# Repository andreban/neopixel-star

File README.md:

# NeoPixel Star

A star-shaped NeoPixel board in the spirit of the Adafruit Jewel. The outline is the exact yellow
sparkle from the [Modern Web Guidance logo](reference/mwg-logo.svg), uniformly scaled. Nine
addressable RGB LEDs: one in the centre, one in each of the 8 points.

| SMD ([smd/](smd/README.md)) | Hot-plate ([hotplate/](hotplate/README.md): [v1](hotplate/v1/README.md) / [v2](hotplate/v2/README.md)) | Through-hole ([tht/](tht/README.md)) | XIAO ([xiao/](xiao/README.md)) |
|---|---|---|---|
|  |  |  |  |
| 50 mm · 9 × WS2812B (5050) | 50 mm · 9 × WS2812B-Mini (3535) | 55 mm · 9 × WS2812D-F5 (5 mm) | 60 mm · 9 × WS2812B-Mini (3535) |
| Fab-assembled, parts on both sides | Front reflowed on a hot plate, back soldered by iron | Hand-soldered | Hot-plate front, Seeed XIAO plugged into female headers on the back |
| 74AHCT1G125 level shifter, 100 nF per LED | 0603 passives; [v1](hotplate/v1/README.md) with level shifter, [v2](hotplate/v2/README.md) direct 3.3 V data | LEDs take 3.3 V data directly | Own microcontroller: plug in USB-C and program it |

All versions share:

- A JST-PH 2.0 mm 3-pin connector on the back, cable toward the top point, pins labelled `5V / DIN / GND`
  (except the XIAO version, which has a USB-C microcontroller board there instead)
- Yellow solder mask, black silkscreen, ENIG, with the MWG logo in exposed gold on the back
- 2 layers, 1.6 mm. Front is a solid 5 V pour, back a solid GND pour
- The same data order, so the same code drives any of them

> **Status:** all designs pass KiCad ERC and DRC, including a check that each board matches its
> schematic. None has been manufactured or tested yet. Treat the first order as a prototype run.

## Wiring

The [XIAO version](xiao/README.md) needs none: it has its own microcontroller and USB-C. The others
connect through J1:

| J1 pin | Signal | Connect to |
|---|---|---|
| 1 | 5V | MCU board's 5 V / VBUS / USB pin, or an external 5 V supply |
| 2 | DIN | Any GPIO (3.3 V or 5 V logic) |
| 3 | GND | GND |

The data chain is: LED1 in the centre, then the top point, then clockwise (index 0 = centre,
1 = top, 2 = top-right, … 8 = top-left).

Minimal Arduino sketch ([Adafruit NeoPixel](https://github.com/adafruit/Adafruit_NeoPixel)):

```cpp
#include <Adafruit_NeoPixel.h>

Adafruit_NeoPixel star(9, /* DIN pin */ 6, NEO_GRB + NEO_KHZ800);

void setup() {
  star.begin();
  star.setBrightness(80);  // keep USB-powered boards within budget, see below
}

void loop() {
  for (int i = 0; i < 9; i++) {          // light each LED in turn, centre first
    star.clear();
    star.setPixelColor(i, star.Color(255, 180, 0));
    star.show();
    delay(200);
  }
}
```

**Power:** at full white each board draws about 540 mA, which is more than many USB ports and
cables supply. When powering from the MCU's USB 5 V pin, cap the brightness in software:

```cpp
strip.setBrightness(80);                        // Adafruit_NeoPixel, 0-255
FastLED.setMaxPowerInVoltsAndMilliamps(5, 400); // FastLED
```

Don't power it from a 3V3 pin. The LEDs need 3.7–5.3 V, and a 3.3 V regulator can't supply the current.

## Ordering

Each version has its own Gerbers in `<version>/fab/`, which work at both JLCPCB and PCBWay.
Silkscreen colour is an order option, not part of the files.

**Board options:** 2 layers · 1.6 mm FR-4 · **yellow** solder mask · **black** silkscreen ·
**ENIG** surface finish (this is what makes the logo gold) · 1 oz copper.

Version-specific steps, BOM and placement files: [SMD](smd/README.md#ordering) ·
[hot-plate v1](hotplate/v1/README.md#ordering) / [v2](hotplate/v2/README.md#ordering) · [through-hole](tht/README.md#ordering).

## Opening in KiCad or EasyEDA

Each version is a self-contained KiCad 10 project in `<version>/kicad/`. Its symbols and footprints
come from the project's own libraries, so no global libraries are needed. `<version>/easyeda/` has
the project zipped for EasyEDA Pro (*File → Import → KiCad*) and the exact outline as DXF. See the
[SMD notes](smd/README.md#opening-in-kicad-or-easyeda) for EasyEDA's via rule and expected warnings.

## Repository layout

| Path | Contents |
|---|---|
| `smd/`, `hotplate/v1/`, `hotplate/v2/`, `tht/`, `xiao/` | One folder per version: `README.md`, `kicad/` (project and libraries), `fab/` (Gerbers, BOM, placement), `easyeda/`, `docs/` (renders, assembly drawings, schematic PDF) |
| `scripts/` | Generators: everything in the version folders except the READMEs is built from these |
| `scripts/common/` | Code shared by all versions: outline, logo, design rules, board and schematic helpers |
| `scripts/smd/`, `scripts/hotplate/v1/`, `scripts/hotplate/v2/`, `scripts/tht/`, `scripts/xiao/` | Per version: `parts.py` (parts and nets), `layout.py` (placement and routing), `schematic.py` |
| `reference/` | The source logo SVG |
| `PLAN.md` | Design decisions and their reasoning |
| `AGENTS.md` | How to change the design (for AI agents and humans) |

## Rebuilding

KiCad 10 must be installed. It is found in its standard install location, or set `KICAD_DIR` to the
installation directory.

```sh
python scripts/build_all.py          # all versions
python scripts/build_all.py tht      # one version: smd, hotplate, hotplate/v1, hotplate/v2, tht or xiao
```

For each version, this regenerates the schematic and board, refills the pours with KiCad's zone
filler, and runs ERC and DRC with schematic parity. The build stops on any violation. It then
exports the Gerbers, the JLCPCB/PCBWay BOM and placement files, the EasyEDA package, the renders and
the assembly drawings (SVG, plus a printable PDF).

## Credits

The board outline and back-side artwork use the Modern Web Guidance logo from
[developer.chrome.com](https://developer.chrome.com/). Inspired by the
[Adafruit NeoPixel Jewel](https://www.adafruit.com/product/2226).

## License

[Apache License 2.0](LICENSE).

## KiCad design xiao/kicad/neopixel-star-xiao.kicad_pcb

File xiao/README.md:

# NeoPixel Star: XIAO version

A self-contained star: a [Seeed Studio XIAO](https://wiki.seeedstudio.com/SeeedStudio_XIAO_Series_Introduction/)
on the back runs the LEDs and connects over its own USB-C. No separate microcontroller, no cable to
wire up. The front is the [hot-plate v2](../hotplate/v2/README.md) design (3535 LEDs that take
3.3 V data directly), so it reflows the same way. The XIAO plugs into two female headers on the
back, so it can come out again (to reuse it, or swap in another model). 60 mm.

| Front | Back |
|---|---|
|  |  |
|  |  |
|  |  |

Schematic: [docs/schematic.pdf](docs/schematic.pdf)

Assembly drawing, front and back, for printing: [docs/assembly.pdf](docs/assembly.pdf)

> **Status:** passes KiCad ERC and DRC, including schematic parity. Not manufactured or tested yet.

## Which XIAO

Any of them. All XIAO boards share the same 14 edge pins (`D0`–`D10`, `3V3`, `GND`, `5V`), and the
board only uses three: `5V`, `GND` and `D3`. The pads some models have underneath aren't used.

The two Raspberry Pi ones are the obvious choice. Both are cheap and well supported in Arduino,
MicroPython and CircuitPython:

| XIAO | Seeed SKU | LCSC | `D3` is |
|---|---|---|---|
| RP2350 (in the BOM) | 102010550 | C41882923 | GPIO5 |
| RP2040 | 102010428 | C22184628 | GPIO29 |

The ESP32-C3/C6/S3 and nRF52840 XIAOs work the same way.

## How it differs from hot-plate v2

- **No J1.** Power and data come from the XIAO: its `5V` pin is USB VBUS, and its `D3` drives the
  chain through `R1` (330 Ω). The WS2812B-MINI-V6 switches at $0.55 \times V_{DD}$ ($2.75\text{ V}$
  at $5\text{ V}$), so the XIAO's 3.3 V output drives it directly.
- **60 mm instead of 50 mm.** The XIAO's pin rows are 15.24 mm apart, through the middle of the
  board. The LED ring, its vias and the back-side data hops are v2's, scaled up so they clear the
  pins.
- **In female headers, not flat.** A USB-C plug's moulded grip is about 12.5 × 6.5 mm. Soldered
  flat, the plug would hit the board, because the notches between the points are too narrow for it,
  and cutting a slot for it wrecks the logo's shape. The headers lift the module 11 mm (8.5 mm socket
  plus the XIAO's 2.5 mm header plastic), so any plug clears the board. The module's top is about
  14.5 mm above the star's back. Vias are tented, so they can sit under the module.
- **Artwork all on the front.** The module covers the back. The credit line sits above the pin rows,
  the gold logo between them, and the title (0.9 mm instead of 1 mm, to fit) below them.

## Parts

| Ref | Side | Part | LCSC |
|---|---|---|---|
| LED1–LED9 | front | Worldsemi WS2812B-MINI-V6, 3535 | C52941386 |
| C1 | front | 10 µF 0603 X5R (Samsung CL10A106KP8NNNC) | C19702 |
| R1 | front | 330 Ω 0603 (UNI-ROYAL 0603WAF3300T5E) | C23138 |
| U1 | back | Seeed Studio XIAO RP2350 (102010550), or XIAO RP2040 (102010428, C22184628), or any XIAO | C41882923 |
| — | back | 2 × 1x7 female header, 2.54 mm, 8.5 mm tall (HCTL PM254-1-07-Z-8.5) | C2897370 |
| — | on the XIAO | 2 × 1x7 male pin header, 2.54 mm, 2.5 mm plastic (HCTL PZ254-1-07-Z-8.5) | C2894930 |

## Assembly

1. **Bake the LEDs first.** They are moisture-sensitive (MSL 5a): 120 °C for 4 hours for loose
   parts (or 70–75 °C for 24 hours), then solder them within 24 hours.
2. **Front, on the hot plate.** Order a solder-paste stencil with the boards (front side only).
   Paste the front, then place R1, C1 and the 9 LEDs. Each LED's pin-1 corner matches the `1` on
   its silkscreen outline. Reflow with the back of the board flat on the plate. Aim for a 245 °C
   peak and don't linger: about 45–90 s above 217 °C.
3. **Male headers on the XIAO.** Plug the two male headers into the female ones so they stay
   straight and parallel, then put the XIAO on top, component side up, and solder its 14 pins.
4. **Female headers on the star, with an iron.** Push the female headers' pins through the star
   from the back, with the XIAO still plugged in as a jig and its USB-C toward the top point (the
   outline on the back silkscreen shows where). Solder the 14 pins on the star's front and trim
   them flush.
5. Unplug the XIAO and check with a multimeter that 5V and GND aren't shorted, then plug it back
   in.

## Code

Same data order as the other versions: index 0 is the centre, 1 the top point, then clockwise. Data
is on `D3`. With [Adafruit NeoPixel](https://github.com/adafruit/Adafruit_NeoPixel) in Arduino:

```cpp
#include <Adafruit_NeoPixel.h>

Adafruit_NeoPixel star(9, D3, NEO_GRB + NEO_KHZ800);

void setup() {
  star.begin();
  star.setBrightness(80);  // USB-powered: stay within the port's budget
}

void loop() {
  for (int i = 0; i < 9; i++) {
    star.clear();
    star.setPixelColor(i, star.Color(255, 180, 0));
    star.show();
    delay(200);
  }
}
```

In CircuitPython it's `neopixel.NeoPixel(board.D3, 9)`. MicroPython uses GPIO numbers:

```python
neopixel.NeoPixel(machine.Pin(5), 9)   # XIAO RP2350
neopixel.NeoPixel(machine.Pin(29), 9)  # XIAO RP2040
```

**Power:** the LEDs draw from USB through the XIAO's `5V` pin, up to about 540 mA at full white.
That's more than a USB 2.0 port is required to supply, so cap the brightness (above) or with
`FastLED.setMaxPowerInVoltsAndMilliamps(5, 400)`.

## Ordering

`fab/neopixel-star-xiao-gerbers.zip`, with the board options from the
[main README](../README.md#ordering). Add a **stencil for the front (top) layer**. `fab/jlcpcb/` and
`fab/pcbway/` also have BOM and placement files if you'd rather have the front assembled. Leave U1
out of the assembly order and solder it yourself.

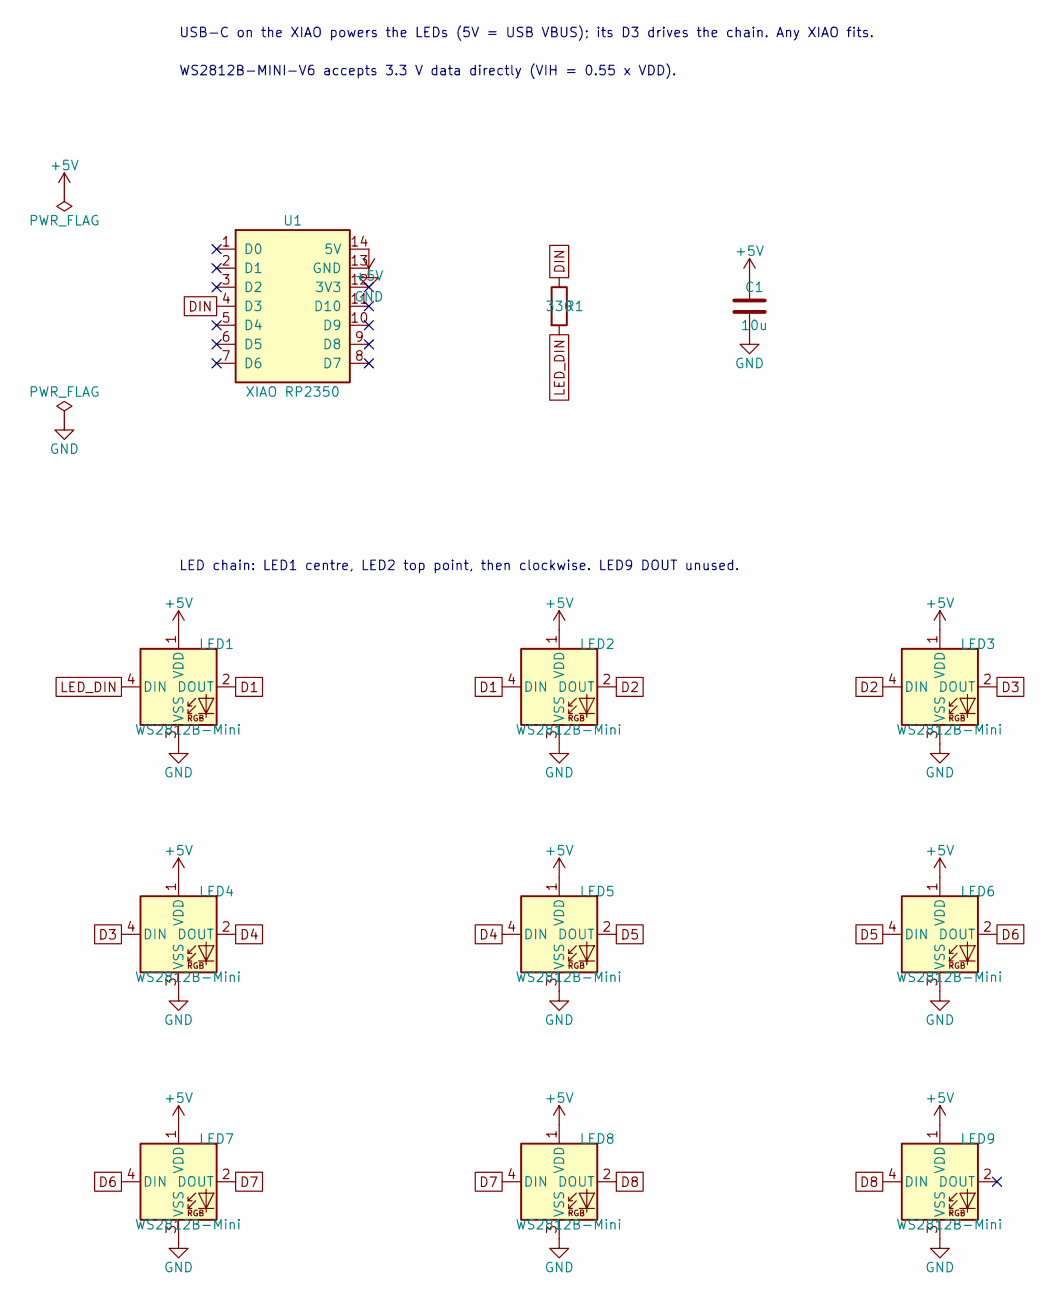
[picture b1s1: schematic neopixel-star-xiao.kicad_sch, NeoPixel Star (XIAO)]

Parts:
C1: 10u; C_0603_1608Metric; MPN CL10A106KP8NNNC; LCSC C19702
LED1, LED2, LED3, LED4, LED5, LED6, LED7, LED8, LED9: WS2812B-Mini; LED_WS2812B-Mini_PLCC4_3.5x3.5mm; MPN WS2812B-MINI-V6; LCSC C52941386
R1: 330; R_0603_1608Metric; MPN 0603WAF3300T5E; LCSC C23138
U1: XIAO RP2350; XIAO_Socket_2x07_P2.54mm_W15.24mm; MPN 102010550; LCSC C41882923

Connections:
+5V: C1.1, LED1.1 (VDD), LED2.1 (VDD), LED3.1 (VDD), LED4.1 (VDD), LED5.1 (VDD), LED6.1 (VDD), LED7.1 (VDD), LED8.1 (VDD), LED9.1 (VDD), U1.14 (5V)
D1: LED1.2 (DOUT), LED2.4 (DIN)
D2: LED2.2 (DOUT), LED3.4 (DIN)
D3: LED3.2 (DOUT), LED4.4 (DIN)
D4: LED4.2 (DOUT), LED5.4 (DIN)
D5: LED5.2 (DOUT), LED6.4 (DIN)
D6: LED6.2 (DOUT), LED7.4 (DIN)
D7: LED7.2 (DOUT), LED8.4 (DIN)
D8: LED8.2 (DOUT), LED9.4 (DIN)
DIN: R1.1, U1.4 (D3)
GND: C1.2, LED1.3 (VSS), LED2.3 (VSS), LED3.3 (VSS), LED4.3 (VSS), LED5.3 (VSS), LED6.3 (VSS), LED7.3 (VSS), LED8.3 (VSS), LED9.3 (VSS), U1.13 (GND)
LED_DIN: LED1.4 (DIN), R1.2

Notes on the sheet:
USB-C on the XIAO powers the LEDs (5V = USB VBUS); its D3 drives the chain. Any XIAO fits.
WS2812B-MINI-V6 accepts 3.3 V data directly (VIH = 0.55 x VDD).
LED chain: LED1 centre, LED2 top point, then clockwise. LED9 DOUT unused.

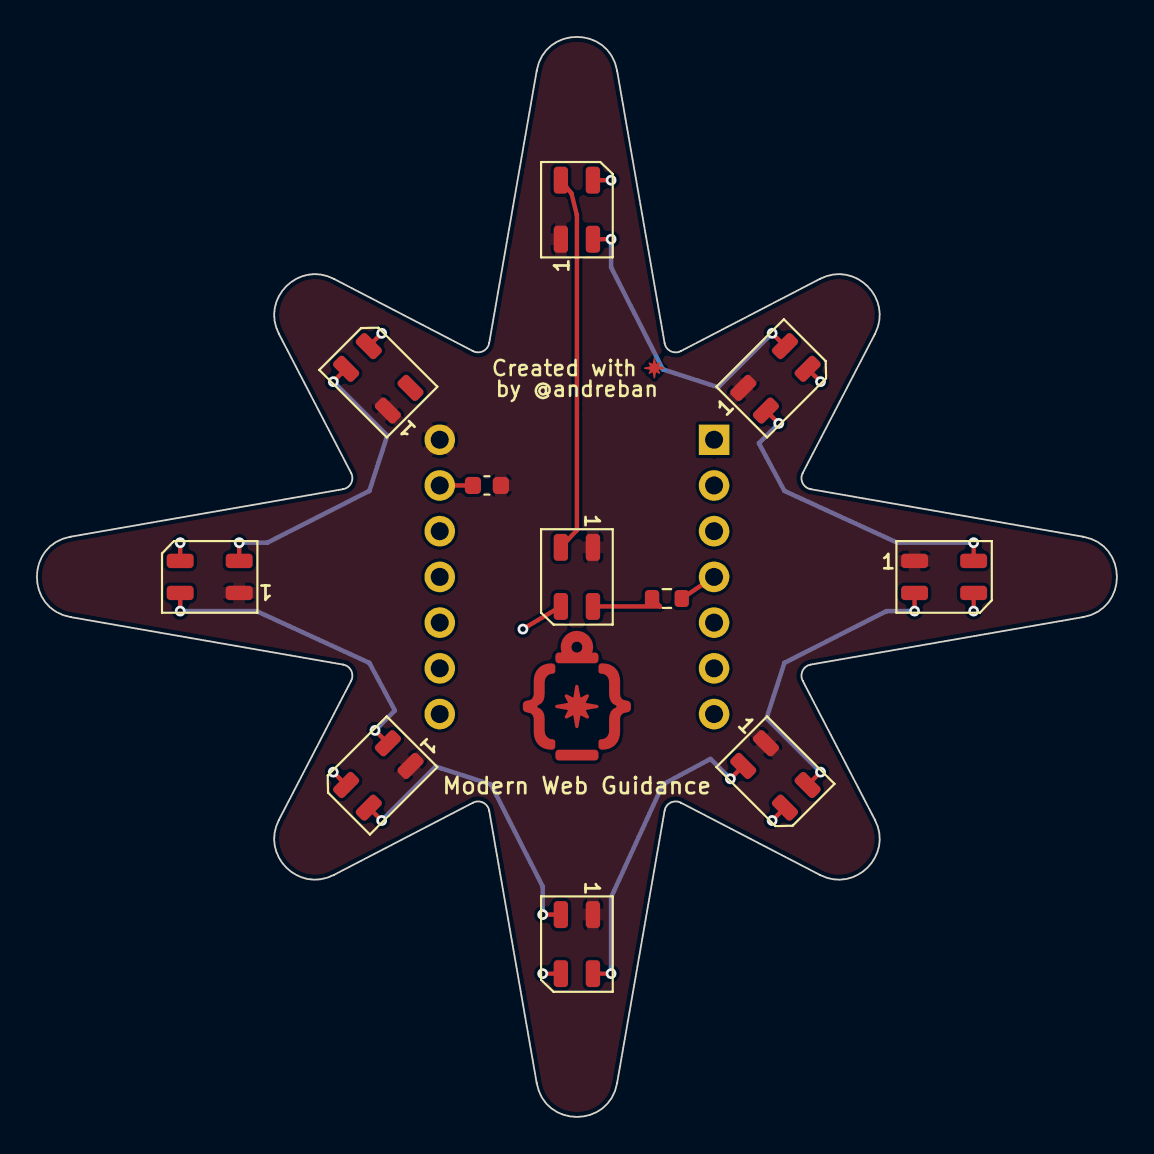
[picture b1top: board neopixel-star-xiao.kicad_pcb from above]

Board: 2 copper layers, 60.0 x 60.0 mm, 12 parts (1 on the bottom side), 12 nets.

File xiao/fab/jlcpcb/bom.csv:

Comment,Designator,Footprint,LCSC Part #
10u,C1,C_0603_1608Metric,C19702
WS2812B-Mini,"LED1,LED2,LED3,LED4,LED5,LED6,LED7,LED8,LED9",LED_WS2812B-Mini_PLCC4_3.5x3.5mm,C52941386
330,R1,R_0603_1608Metric,C23138
XIAO RP2350,U1,XIAO_Socket_2x07_P2.54mm_W15.24mm,C41882923

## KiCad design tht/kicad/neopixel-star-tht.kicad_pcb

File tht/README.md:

# NeoPixel Star: through-hole version

A hand-solderable version of the [NeoPixel Star](../README.md): the same outline, artwork, wiring and
data order, built from through-hole parts. It is **55 mm** tip to tip (the SMD board is 50 mm).

| Front | Back |
|---|---|
|  |  |
|  |  |
|  |  |

Schematic: [docs/schematic.pdf](docs/schematic.pdf)

Assembly drawing, front and back, for printing: [docs/assembly.pdf](docs/assembly.pdf)

> **Status:** passes KiCad ERC and DRC, including schematic parity. Not manufactured or tested yet.

## How it differs from the SMD board

- **LEDs:** 9 × Worldsemi **WS2812D-F5** (5 mm, 4 leads). Their data input threshold is a fixed
  2.7 V, so **3.3 V microcontrollers drive them directly**. No level shifter, and the LEDs run at a
  full 5 V.
- **No per-LED capacitors:** the WS2812D-F5 datasheet calls for none. There is one 10 µF bulk
  capacitor at the input.
- **Parts on the front, soldered from the back.** The exception is the connector: it sits on the
  back, with the cable exiting toward the top point, and its 3 pins are soldered from the front.
- **Staggered LED footprint.** The WS2812D-F5 leads are 1.27 mm apart. Inline pads at that pitch
  leave too thin a copper ring, so the footprint staggers alternate leads by 1.52 mm: the leads
  zig-zag (see Assembly).
- **Size:** 55 mm, because at 50 mm the LEDs only fit pulled in so far that the top LED's leads end
  up under the connector.
- **Front silkscreen:** each LED has a short line marking where its **flat side** goes (pin 1).
  The electrolytic capacitor's `+` and the outlines of R1 and C1 are also marked.

## Parts

| Ref | Part | LCSC |
|---|---|---|
| LED1–LED9 | Worldsemi WS2812D-F5, 5 mm | C190565 |
| C1 | 10 µF 25 V electrolytic, 5 × 11 mm, 2 mm lead spacing | C43347 |
| R1 | 330 Ω ¼ W metal film, mounted upright | C119313 |
| J1 | JST S3B-PH-K-S (PH, 3-pin, side entry) | C157929 |

Any 5 mm WS2812D-F5-compatible LED works **only if its pinout is 1 DOUT, 2 VDD, 3 GND, 4 DIN**.
Other 5 mm addressable LEDs order their leads differently: some swap VDD and GND (APA106, a short
across the supply), others swap the data pins (the chain doesn't light).

## Assembly

1. **R1 and C1 first.** C1's longer lead (`+`) goes in the square pad.
2. **LEDs:** bend the leads into a zig-zag just below the body: pins 1 and 3 about 0.8 mm one
   way, pins 2 and 4 about 0.8 mm the other way. Insert with the LED's flat side over the short
   silkscreen line (pin 1), seat it level, and solder from the back.
3. **J1 last:** it goes on the **back**, with its opening facing the top point. Solder its 3 pins
   from the front.
4. Before powering it up, check with a multimeter that 5V and GND aren't shorted.

Wiring and power are the same as the SMD board: 5V / DIN / GND on J1 (labelled on the back),
data order centre first, then clockwise from the top point. See the [main README](../README.md#wiring).

## Ordering

`fab/neopixel-star-tht-gerbers.zip` with the board options from the
[main README](../README.md#ordering). Most through-hole builds are hand-soldered, but
`fab/jlcpcb/` and `fab/pcbway/` have BOM and placement files for through-hole assembly too.

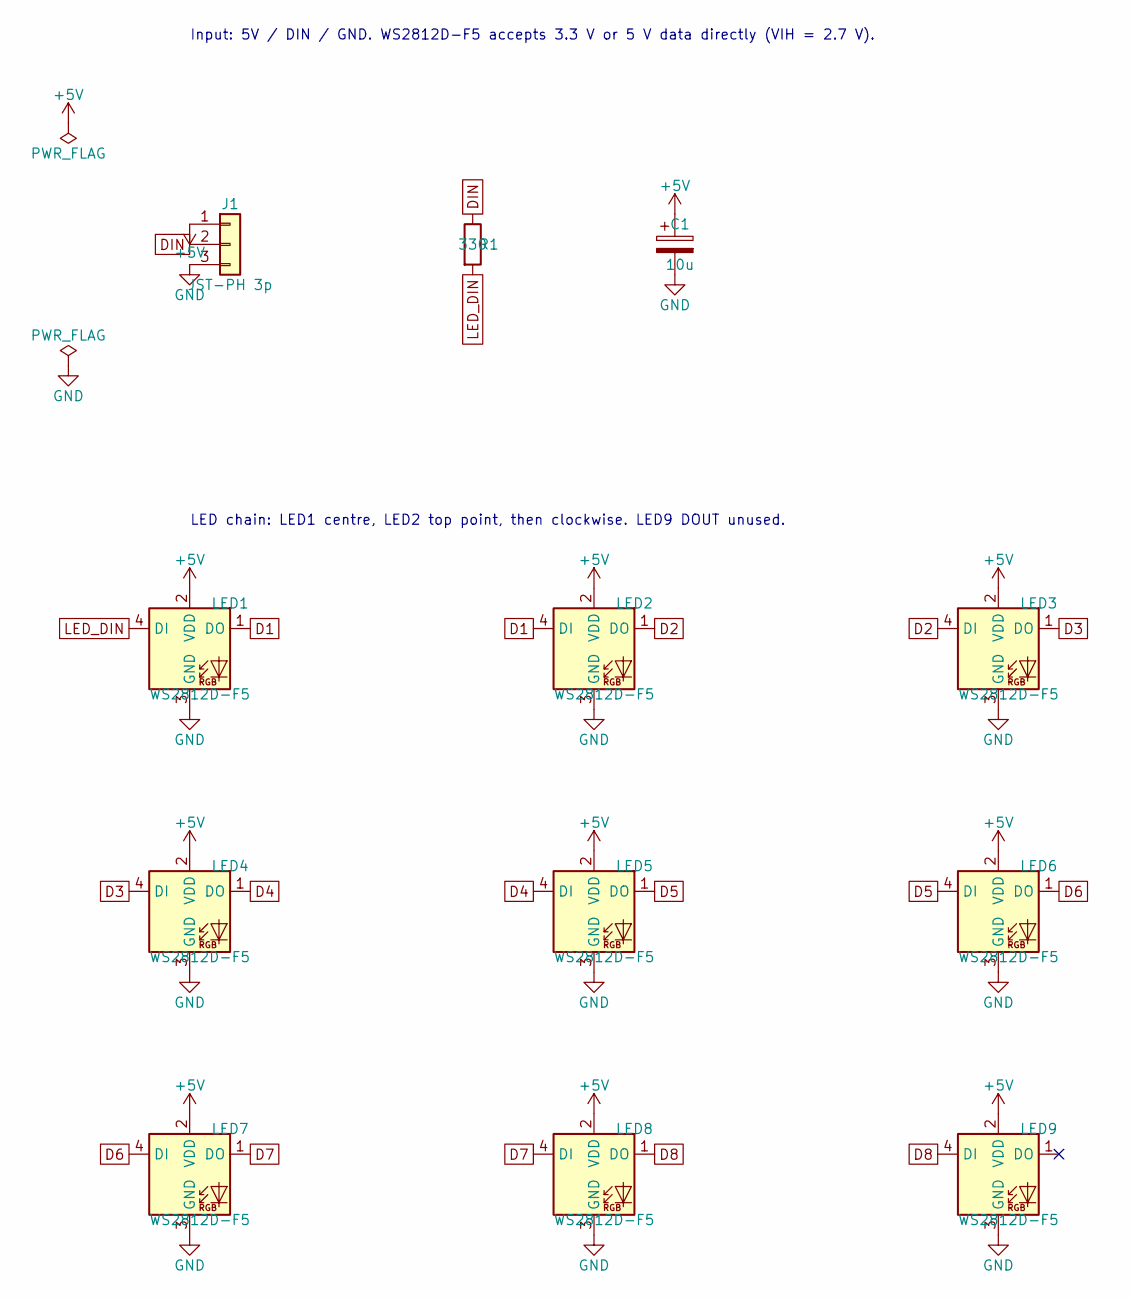
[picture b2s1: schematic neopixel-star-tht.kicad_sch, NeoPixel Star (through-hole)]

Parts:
C1: 10u; CP_Radial_D5.0mm_P2.00mm; MPN KM106M025D11RR0VH2FP0; LCSC C43347
J1: JST-PH 3p; JST_PH_S3B-PH-K_1x03_P2.00mm_Horizontal; MPN S3B-PH-K-S(LF)(SN); LCSC C157929
LED1, LED2, LED3, LED4, LED5, LED6, LED7, LED8, LED9: WS2812D-F5; LED_D5.0mm-4_RGB_Staggered_Pins; MPN WS2812D-F5; LCSC C190565
R1: 330; R_Axial_DIN0207_L6.3mm_D2.5mm_P2.54mm_Vertical; MPN MF1/4W-330R 1%; LCSC C119313

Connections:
+5V: C1.1, J1.1, LED1.2 (VDD), LED2.2 (VDD), LED3.2 (VDD), LED4.2 (VDD), LED5.2 (VDD), LED6.2 (VDD), LED7.2 (VDD), LED8.2 (VDD), LED9.2 (VDD)
D1: LED1.1 (DO), LED2.4 (DI)
D2: LED2.1 (DO), LED3.4 (DI)
D3: LED3.1 (DO), LED4.4 (DI)
D4: LED4.1 (DO), LED5.4 (DI)
D5: LED5.1 (DO), LED6.4 (DI)
D6: LED6.1 (DO), LED7.4 (DI)
D7: LED7.1 (DO), LED8.4 (DI)
D8: LED8.1 (DO), LED9.4 (DI)
DIN: J1.2, R1.1
GND: C1.2, J1.3, LED1.3 (GND), LED2.3 (GND), LED3.3 (GND), LED4.3 (GND), LED5.3 (GND), LED6.3 (GND), LED7.3 (GND), LED8.3 (GND), LED9.3 (GND)
LED_DIN: LED1.4 (DI), R1.2

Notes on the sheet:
Input: 5V / DIN / GND. WS2812D-F5 accepts 3.3 V or 5 V data directly (VIH = 2.7 V).
LED chain: LED1 centre, LED2 top point, then clockwise. LED9 DOUT unused.

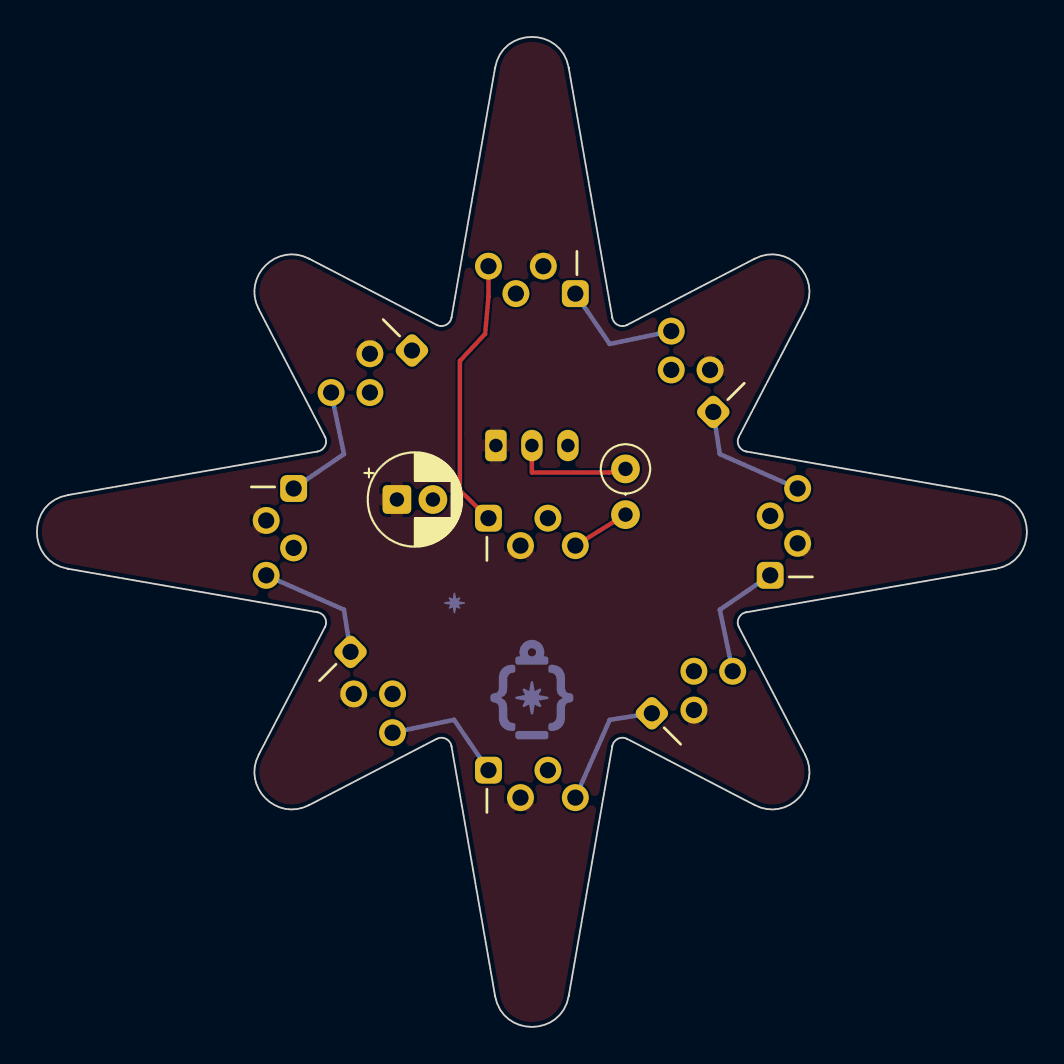
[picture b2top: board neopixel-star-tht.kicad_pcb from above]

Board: 2 copper layers, 55.0 x 55.0 mm, 12 parts (1 on the bottom side), 12 nets.
